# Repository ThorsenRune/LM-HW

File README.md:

# LM-HW
Design files for the LM project
First Version of the LM Hardware

This hardware is part of a neuroprosthesis aimed at restoring hand function in people with tetraplegia.
It is a two channel emg amplifier and a two channel functional electrical stimulator controlled by the ADUCM360 microcontroller.
These are realized using the Eagle version 7 and produced and assembled by EuroCircuits.
The circuits are tested and functional with some minor bug fixes. 

Bug fixes are available upon request

This part of the LM project has been supported by  The Italian Ministry of Health - Ricerca Corrente, the Promobilia Foundation (Sweden) grant no 16066

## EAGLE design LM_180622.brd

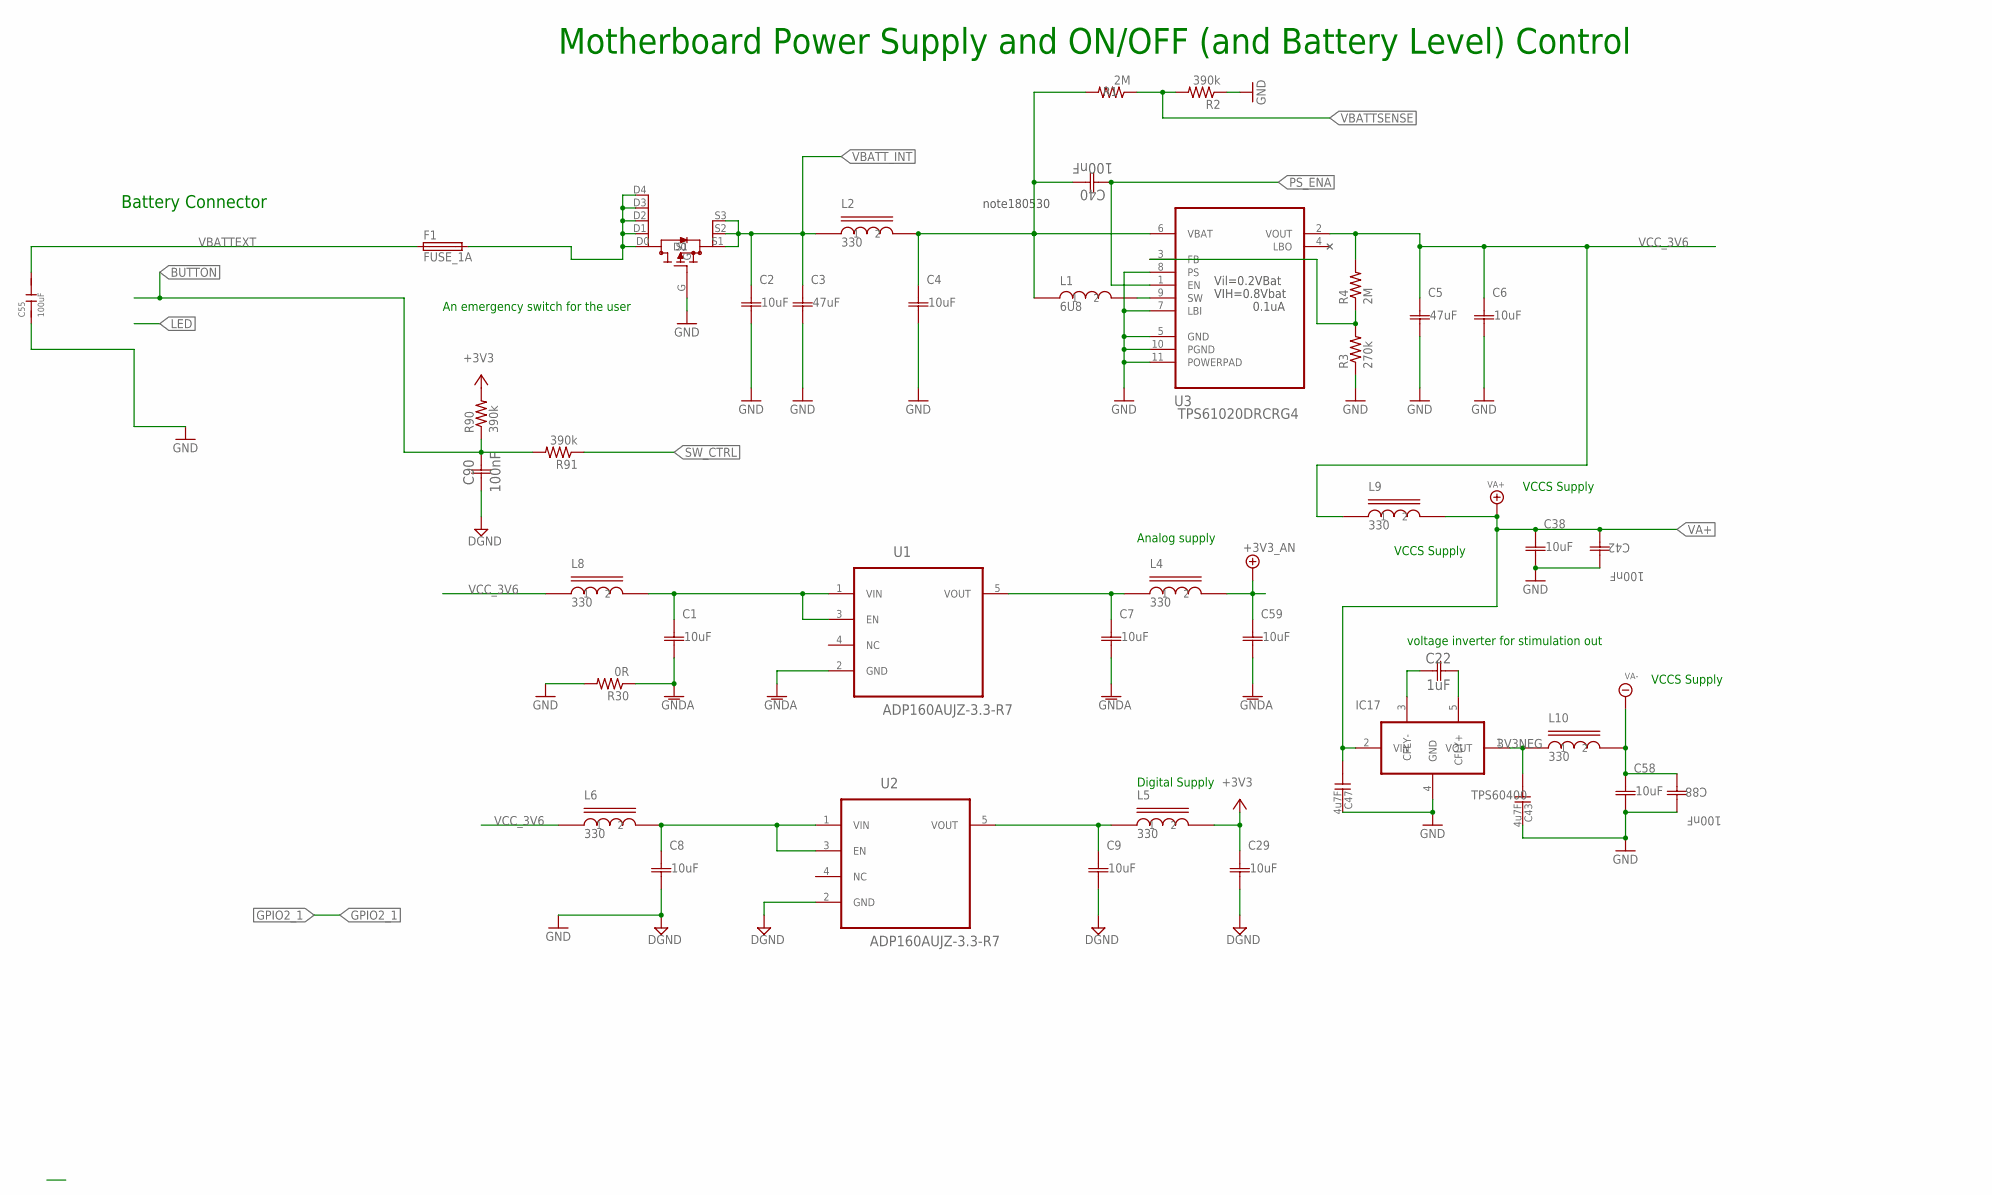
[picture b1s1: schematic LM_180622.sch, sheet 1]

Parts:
C1, C2, C4, C6, C7, C8, C9, C29, C38, C58, C59: 10uF; C0603
C3, C5: 47uF; C0805
C22: 1uF; 0603-CAP
C40, C42, C88, C90: 100nF; C0603
C43, C47: 4u7F; C0805
C55: 100uF; C1210; MPN JMK325BJ107MY-T
F1: FUSE_1A; C0805
IC17: TPS60400; SOT23-5; MPN TPS60400DBVR
L1: 6U8; SMT_POWER_IND_B82462G4; MPN B82462G4682M000
L2, L4, L5, L6, L8, L9, L10: 330; L0603; PARTNO MMZ1608B301C
PMOS1: SIS407DN; POWERPAK1212-8SINGLE
R1, R4: 2M; R0603
R2, R90, R91: 390k; R0603
R3: 270k; R0603; MPN MC0603N270K500CT
R30: 0R; R0603
U1, U2: ADP160AUJZ-3.3-R7; SOT95P280X100-5N; MPN MIC5255-3.3YM5-TR
U3: TPS61020DRCRG4; SON50P300X300X100-11N

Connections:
3V3NEG: C43.1, IC17.1 (VOUT), L10.1
+3V3: C29.2 (C2), L5.2, R90.2; also elsewhere on the board
+3V3_AN: C59.2 (C2), L4.2; also elsewhere on the board
A3V6: C1.2 (C2), L8.2, U1.1 (VIN), U1.3 (EN)
BUTTON: C90.2 (C2), R90.1, R91.2; also elsewhere on the board
FB_3V6: R3.2, R4.1, U3.3 (FB)
GND: C2.1 (C1), C3.1 (C1), C4.1 (C1), C5.1 (C1), C6.1 (C1), C8.1 (C1), C9.1 (C1), C29.1 (C1), C38.1 (C1), C42.2 (C2), C43.2, C47.2, C55.1, C58.1 (C1), C88.2 (C2), C90.1 (C1), IC17.4 (GND), PMOS1.G, R2.1, R3.1, R30.2, U2.2 (GND), U3.5 (GND), U3.7 (LBI), U3.8 (PS), U3.10 (PGND), U3.11 (POWERPAD); also elsewhere on the board
GNDA: C1.1 (C1), C7.1 (C1), C59.1 (C1), R30.1, U1.2 (GND); also elsewhere on the board
unnamed: F1.2, PMOS1.D0, PMOS1.D1, PMOS1.D2, PMOS1.D3, PMOS1.D4
unnamed: L1.2, U3.9 (SW)
unnamed: C7.2 (C2), L4.1, U1.5 (VOUT)
unnamed: C9.2 (C2), L5.1, U2.5 (VOUT)
unnamed: C8.2 (C2), L6.2, U2.1 (VIN), U2.3 (EN)
unnamed: C22.1 (C1), IC17.3 (CFLY-)
unnamed: C22.2 (C2), IC17.5 (CFLY+)
PS_ENA: C40.1 (C1), U3.1 (EN); also elsewhere on the board
SW_CTRL: R91.1; also elsewhere on the board
VA+: C38.2 (C2), C42.1 (C1), C47.1, IC17.2 (VIN), L9.2; also elsewhere on the board
VA-: C58.2 (C2), C88.1 (C1), L10.2; also elsewhere on the board
VBATTEXT: C55.2, F1.1; also elsewhere on the board
VBATTSENSE: R1.1, R2.2; also elsewhere on the board
VBATT_INT: C2.2 (C2), C3.2 (C2), L2.1, PMOS1.S1, PMOS1.S2, PMOS1.S3; also elsewhere on the board
VBATU3: C4.2 (C2), C40.2 (C2), L1.1, L2.2, R1.2, U3.6 (VBAT)
VCC_3V6: C5.2 (C2), C6.2 (C2), L6.1, L8.1, L9.1, R4.2, U3.2 (VOUT)

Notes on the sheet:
Motherboard Power Supply and ON/OFF (and Battery Level) Control
Battery Connector
An emergency switch for the user
voltage inverter for stimulation out
note180530
Vil=0.2VBat
VIH=0.8Vbat
0.1uA
Digital Supply
Analog supply
VCCS Supply

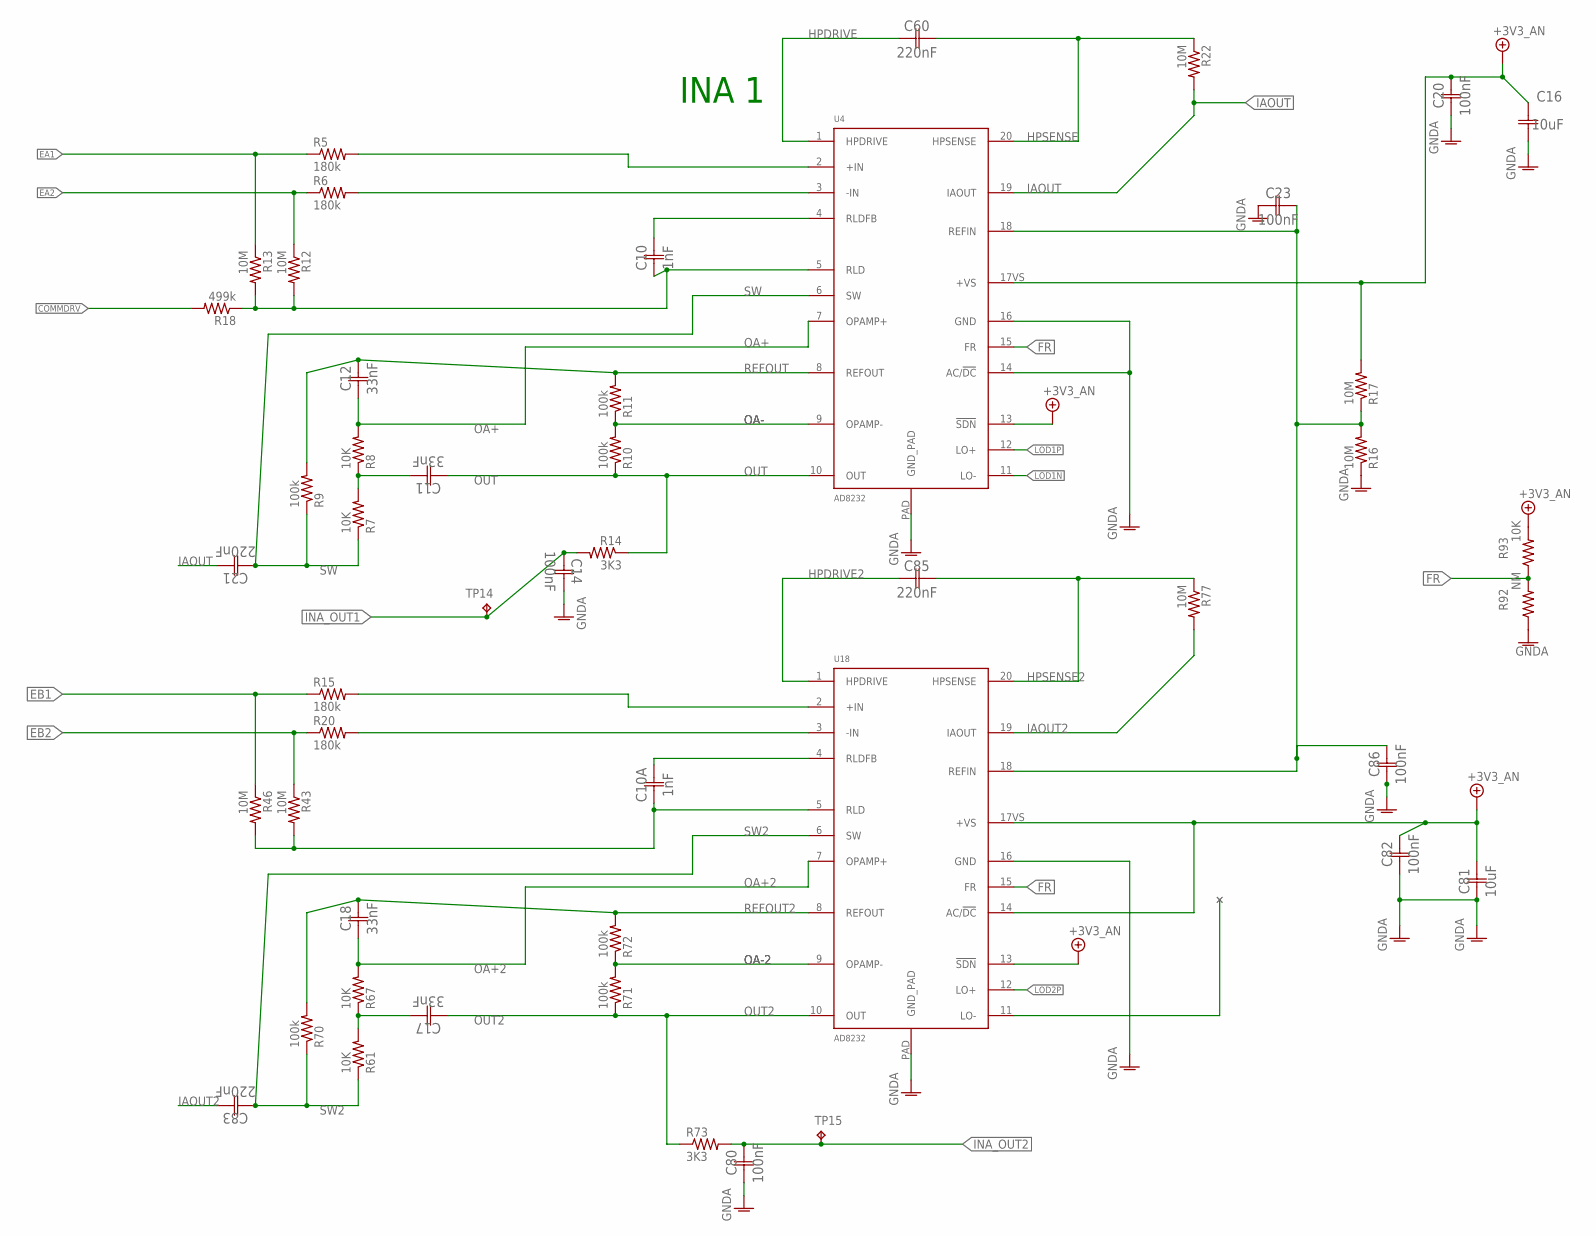
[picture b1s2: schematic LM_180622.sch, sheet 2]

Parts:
C10, C10A: 1nF; C0603
C11, C12, C17, C18: 33nF; C0603
C14, C20, C23, C80, C82, C86: 100nF; C0603
C16, C81: 10uF; C0603
C21, C60, C83, C85: 220nF; C0603
R5, R6, R15, R20: 180k; R0603
R7, R8, R61, R67, R93: 10K; R0603
R9, R10, R11, R70, R71, R72: 100k; R0603
R12, R13, R16, R17, R22, R43, R46, R77: 10M; R0603
R14, R73: 3K3; R0603
R18: 499k; R0603; MPN CRCW0201499KFKED
R92: NM; R0603
TP14, TP15: NM; B1,27
U4, U18: AD8232; LFCSP_20

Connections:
+3V3_AN: C16.2 (C2), C20.1 (C1), C81.2 (C2), C82.1 (C1), R17.2, R93.2, U4.13 (!SDN), U4.17VS (+VS), U18.13 (!SDN), U18.14 (AC/!DC), U18.17VS (+VS); also elsewhere on the board
COMMDRV: R18.2; also elsewhere on the board
EA1: R5.1, R13.1; also elsewhere on the board
EA2: R6.1, R12.1; also elsewhere on the board
EB1: R15.1, R46.1; also elsewhere on the board
EB2: R20.1, R43.1; also elsewhere on the board
FR: R92.2, R93.1, U4.15 (FR), U18.15 (FR)
GNDA: C14.2 (C2), C16.1 (C1), C20.2 (C2), C23.2 (C2), C80.2 (C2), C81.1 (C1), C82.2 (C2), C86.2 (C2), R16.1, R92.1, U4.14 (AC/!DC), U4.16 (GND), U4.PAD (GND_PAD), U18.16 (GND), U18.PAD (GND_PAD); also elsewhere on the board
HPDRIVE: C60.1 (C1), U4.1 (HPDRIVE)
HPDRIVE2: C85.1 (C1), U18.1 (HPDRIVE)
HPSENSE: C60.2 (C2), R22.1, U4.20 (HPSENSE)
HPSENSE2: C85.2 (C2), R77.1, U18.20 (HPSENSE)
IAOUT: C21.1 (C1), R22.2, U4.19 (IAOUT)
IAOUT2: C83.1 (C1), R77.2, U18.19 (IAOUT)
INA_OUT1: C14.1 (C1), R14.2, TP14.TP; also elsewhere on the board
INA_OUT2: C80.1 (C1), R73.2, TP15.TP; also elsewhere on the board
LOD1N: U4.11 (LO-); also elsewhere on the board
LOD1P: U4.12 (LO+); also elsewhere on the board
LOD2P: U18.12 (LO+); also elsewhere on the board
unnamed: R5.2, U4.2 (+IN)
unnamed: R6.2, U4.3 (-IN)
unnamed: C11.1 (C1), R7.2, R8.1
unnamed: C10A.2 (C2), U18.4 (RLDFB)
unnamed: C10A.1 (C1), R43.2, R46.2, U18.5 (RLD)
unnamed: C10.2 (C2), U4.4 (RLDFB)
unnamed: C10.1 (C1), R12.2, R13.2, R18.1, U4.5 (RLD)
unnamed: R15.2, U18.2 (+IN)
unnamed: R20.2, U18.3 (-IN)
unnamed: C17.1 (C1), R61.2, R67.1
OA+: C12.2 (C2), R8.2, U4.7 (OPAMP+)
OA+2: C18.2 (C2), R67.2, U18.7 (OPAMP+)
OA-: R10.2, R11.1, U4.9 (OPAMP-)
OA-2: R71.2, R72.1, U18.9 (OPAMP-)
OUT: C11.2 (C2), R10.1, R14.1, U4.10 (OUT)
OUT2: C17.2 (C2), R71.1, R73.1, U18.10 (OUT)
REFOUT: C12.1 (C1), R9.2, R11.2, U4.8 (REFOUT)
REFOUT2: C18.1 (C1), R70.2, R72.2, U18.8 (REFOUT)
SW: C21.2 (C2), R7.1, R9.1, U4.6 (SW)
SW2: C83.2 (C2), R61.1, R70.1, U18.6 (SW)
VREFIN: C23.1 (C1), C86.1 (C1), R16.2, R17.1, U4.18 (REFIN), U18.18 (REFIN)

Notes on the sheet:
INA 1

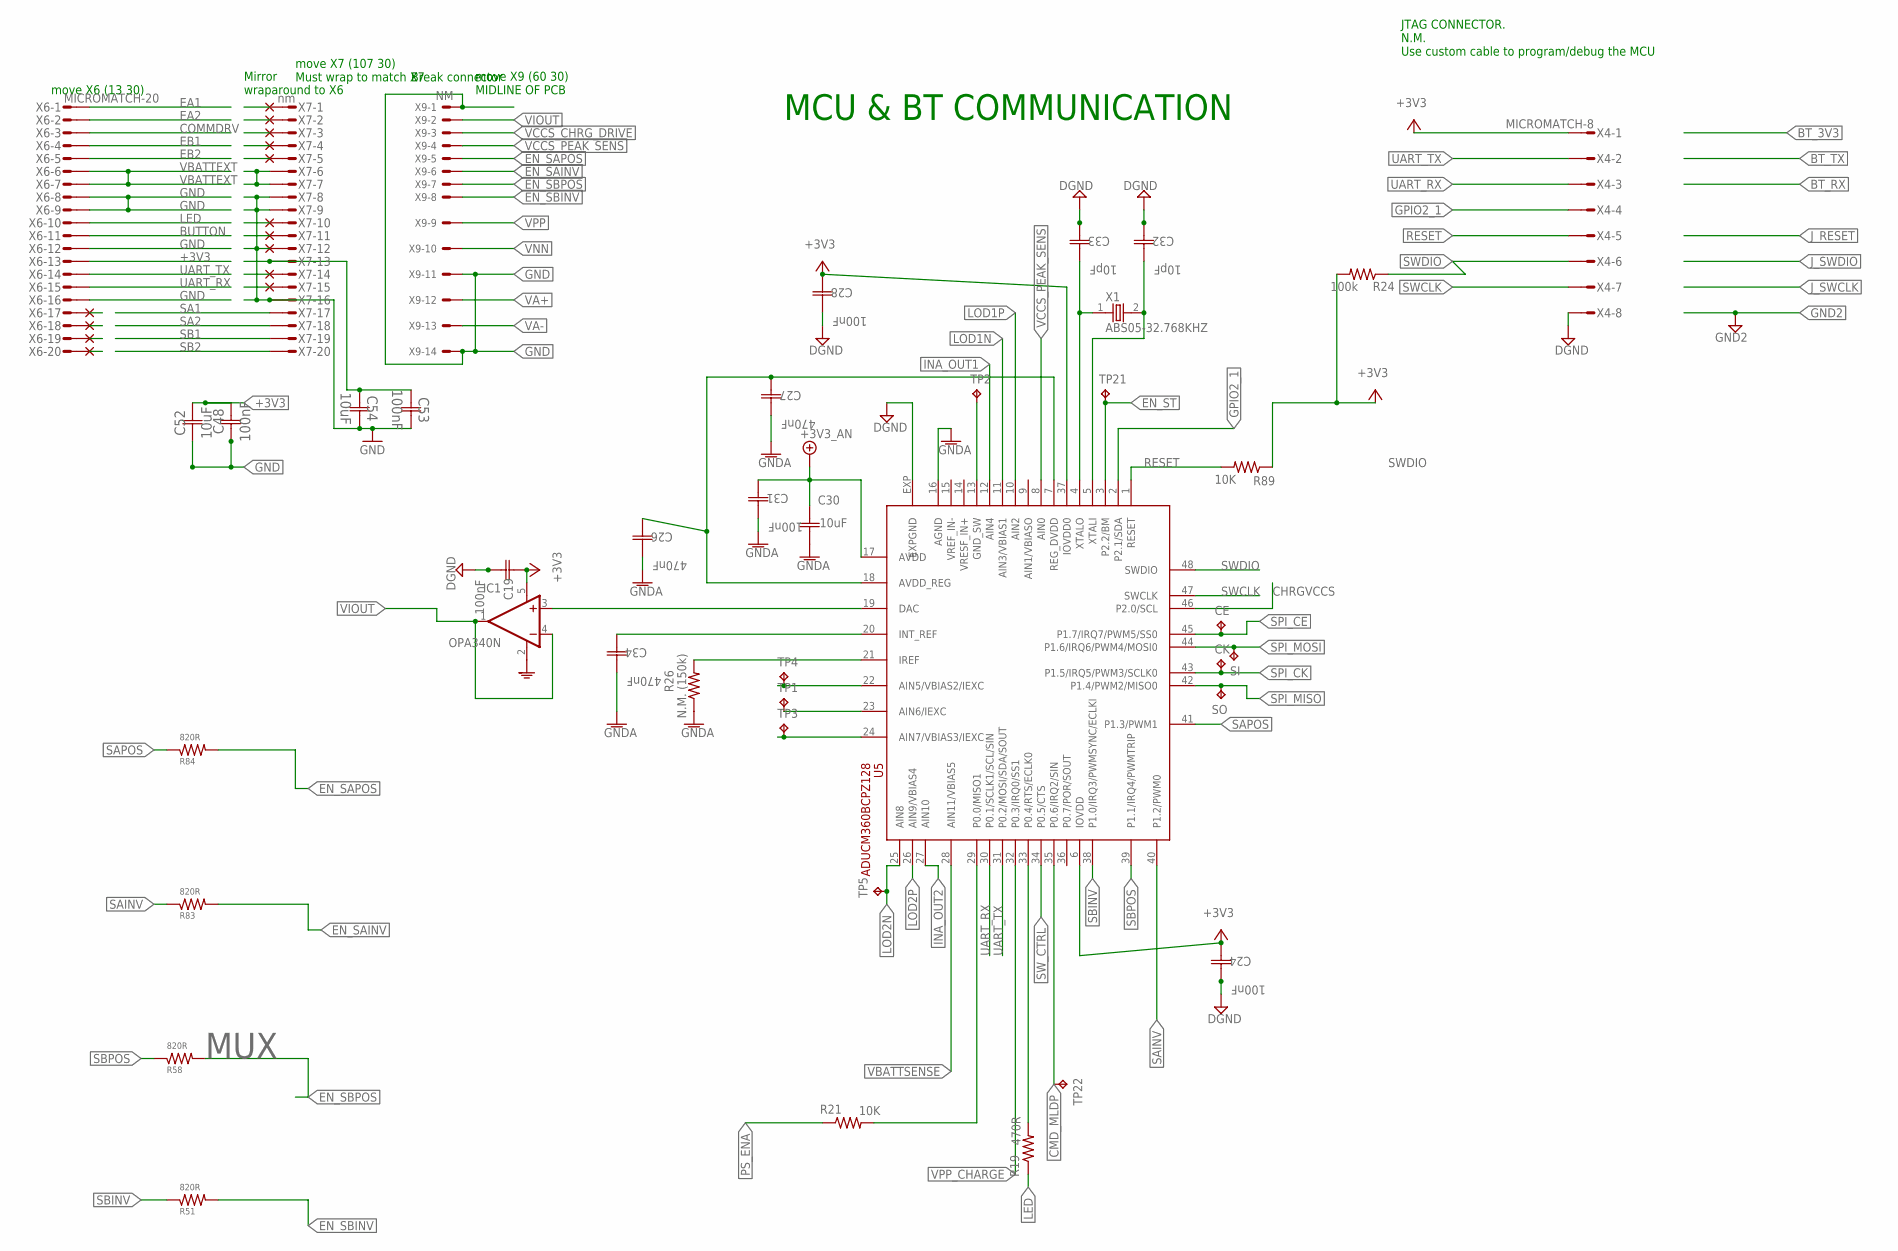
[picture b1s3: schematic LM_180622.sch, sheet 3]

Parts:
C19, C24, C28, C31, C48, C53: 100nF; C0603
C26, C27, C34: 470nF; C0603
C30, C52, C54: 10uF; C0603
C32, C33: 10pF; C0603
CE: NM; TH0305
CK: NM; TH0305
IC1: OPA340N; SOT23-5; MPN OPA340NA/3K
R19: 470R; R0603; MPN ERJ3EKF4700V
R21, R89: 10K; R0603
R24: 100k; R0603
R26: N.M. (150k); R0603
R51, R58, R83, R84: 820R; R0603
SI: NM; TH0305
SO: NM; TH0305
TP1, TP2, TP3, TP4, TP5, TP21, TP22: NM; TH0305
U5: ADUCM360BCPZ128; LFCSP48; MPN ADUCM360BCPZ128
X1: ABS05-32.768KHZ; CRYSTAL-2PIN
X4: MICROMATCH-8
X6: MICROMATCH-20; MPN 2-215079-0
X7: nm; MICROMATCH-20
X9: NM; 70543-14

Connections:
3V3_BT: C53.2 (C2), C54.1 (C1), X7.13
+3V3: C19.1 (C1), C24.1 (C1), C28.1 (C1), C48.1 (C1), C52.2 (C2), IC1.5 (V+), R24.2, R89.1, U5.6 (IOVDD), U5.37 (IOVDD0), X4.1, X6.13; also elsewhere on the board
+3V3_AN: C30.2 (C2), C31.1 (C1), U5.17 (AVDD); also elsewhere on the board
BUTTON: X6.11; also elsewhere on the board
CHRGVCCS: U5.46 (P2.0/SCL); also elsewhere on the board
CMD_MLDP: TP22.TP, U5.35 (P0.6/IRQ2/SIN)
COMMDRV: X6.3; also elsewhere on the board
EA1: X6.1; also elsewhere on the board
EA2: X6.2; also elsewhere on the board
EB1: X6.4; also elsewhere on the board
EB2: X6.5; also elsewhere on the board
EN_SAINV: R83.2, X9.6; also elsewhere on the board
EN_SAPOS: R84.2, X9.5; also elsewhere on the board
EN_SBINV: R51.2, X9.8; also elsewhere on the board
EN_SBPOS: R58.2, X9.7; also elsewhere on the board
EN_ST: TP21.TP, U5.3 (P2.2/BM)
GND: C19.2 (C2), C24.2 (C2), C28.2 (C2), C32.1 (C1), C33.1 (C1), C48.2 (C2), C52.1 (C1), C53.1 (C1), C54.2 (C2), IC1.2 (V-), U5.EXP (EXPGND), X4.8, X6.8, X6.9, X6.12, X6.16, X7.8, X7.9, X7.12, X7.16, X9.1, X9.11, X9.14; also elsewhere on the board
GNDA: C26.2 (C2), C27.2 (C2), C30.1 (C1), C31.2 (C2), C34.2 (C2), R26.1, U5.16 (AGND); also elsewhere on the board
GPIO2_1: U5.2 (P2.1/SDA), X4.4
INA_OUT1: U5.12 (AIN4); also elsewhere on the board
INA_OUT2: U5.27 (AIN10); also elsewhere on the board
LED: R19.1, X6.10
LED_CTRL1: R19.2, U5.33 (P0.4/RTS/ECLK0)
LOD1N: U5.11 (AIN3/VBIAS1); also elsewhere on the board
LOD1P: U5.10 (AIN2); also elsewhere on the board
LOD2N: TP5.TP, U5.25 (AIN8)
LOD2P: U5.26 (AIN9/VBIAS4); also elsewhere on the board
unnamed: C33.2 (C2), U5.4 (XTALO), X1.1
unnamed: C26.1 (C1), C27.1 (C1), U5.7 (REG_DVDD), U5.18 (AVDD_REG)
unnamed: TP1.TP, U5.23 (AIN6/IEXC)
unnamed: C32.2 (C2), U5.5 (XTALI), X1.2
unnamed: R26.2, U5.21 (IREF)
unnamed: C34.1 (C1), U5.20 (INT_REF)
unnamed: R21.2, U5.29 (P0.0/MISO1)
unnamed: TP2.TP, U5.13 (GND_SW)
unnamed: X7.6, X7.7
unnamed: IC1.3 (+IN), U5.19 (DAC)
unnamed: TP3.TP, U5.24 (AIN7/VBIAS3/IEXC)
unnamed: TP4.TP, U5.22 (AIN5/VBIAS2/IEXC)
PS_ENA: R21.1; also elsewhere on the board
RESET: R89.2, U5.1 (RESET), X4.5
SA1: X7.17; also elsewhere on the board
SA2: X7.18; also elsewhere on the board
SAINV: R83.1, U5.40 (P1.2/PWM0)
SAPOS: R84.1, U5.41 (P1.3/PWM1)
SB1: X7.19; also elsewhere on the board
SB2: X7.20; also elsewhere on the board
SBINV: R51.1, U5.38 (P1.0/IRQ3/PWMSYNC/ECLKI)
SBPOS: R58.1, U5.39 (P1.1/IRQ4/PWMTRIP)
SPI_CE: CE.TP, U5.45 (P1.7/IRQ7/PWM5/SS0)
SPI_CK: CK.TP, U5.43 (P1.5/IRQ5/PWM3/SCLK0)
SPI_MISO: SO.TP, U5.42 (P1.4/PWM2/MISO0)
SPI_MOSI: SI.TP, U5.44 (P1.6/IRQ6/PWM4/MOSI0)
SWCLK: U5.47 (SWCLK), X4.7
SWDIO: R24.1, U5.48 (SWDIO), X4.6
SW_CTRL: U5.34 (P0.5/CTS); also elsewhere on the board
UART_RX: U5.30 (P0.1/SCLK1/SCL/SIN), X4.3, X6.15
UART_TX: U5.31 (P0.2/MOSI/SDA/SOUT), X4.2, X6.14
VA+: X9.12; also elsewhere on the board
VA-: X9.13; also elsewhere on the board
VBATTEXT: X6.6, X6.7; also elsewhere on the board
VBATTSENSE: U5.28 (AIN11/VBIAS5); also elsewhere on the board
VCCS_CHRG_DRIVE: X9.3; also elsewhere on the board
VCCS_PEAK_SENS: U5.8 (AIN0), X9.4; also elsewhere on the board
VIOUT: IC1.1 (OUT), IC1.4 (-IN), X9.2; also elsewhere on the board
VNN: X9.10; also elsewhere on the board
VPP: X9.9; also elsewhere on the board
VPP_CHARGE: U5.32 (P0.3/IRQ0/SS1); also elsewhere on the board

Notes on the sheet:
MCU & BT COMMUNICATION
JTAG CONNECTOR. N.M. Use custom cable to program/debug the MCU
MUX
Break connector
Mirror wraparound to X6
move X9 (60 30) MIDLINE OF PCB
move X6 (13 30)
move X7 (107 30) Must wrap to match X7

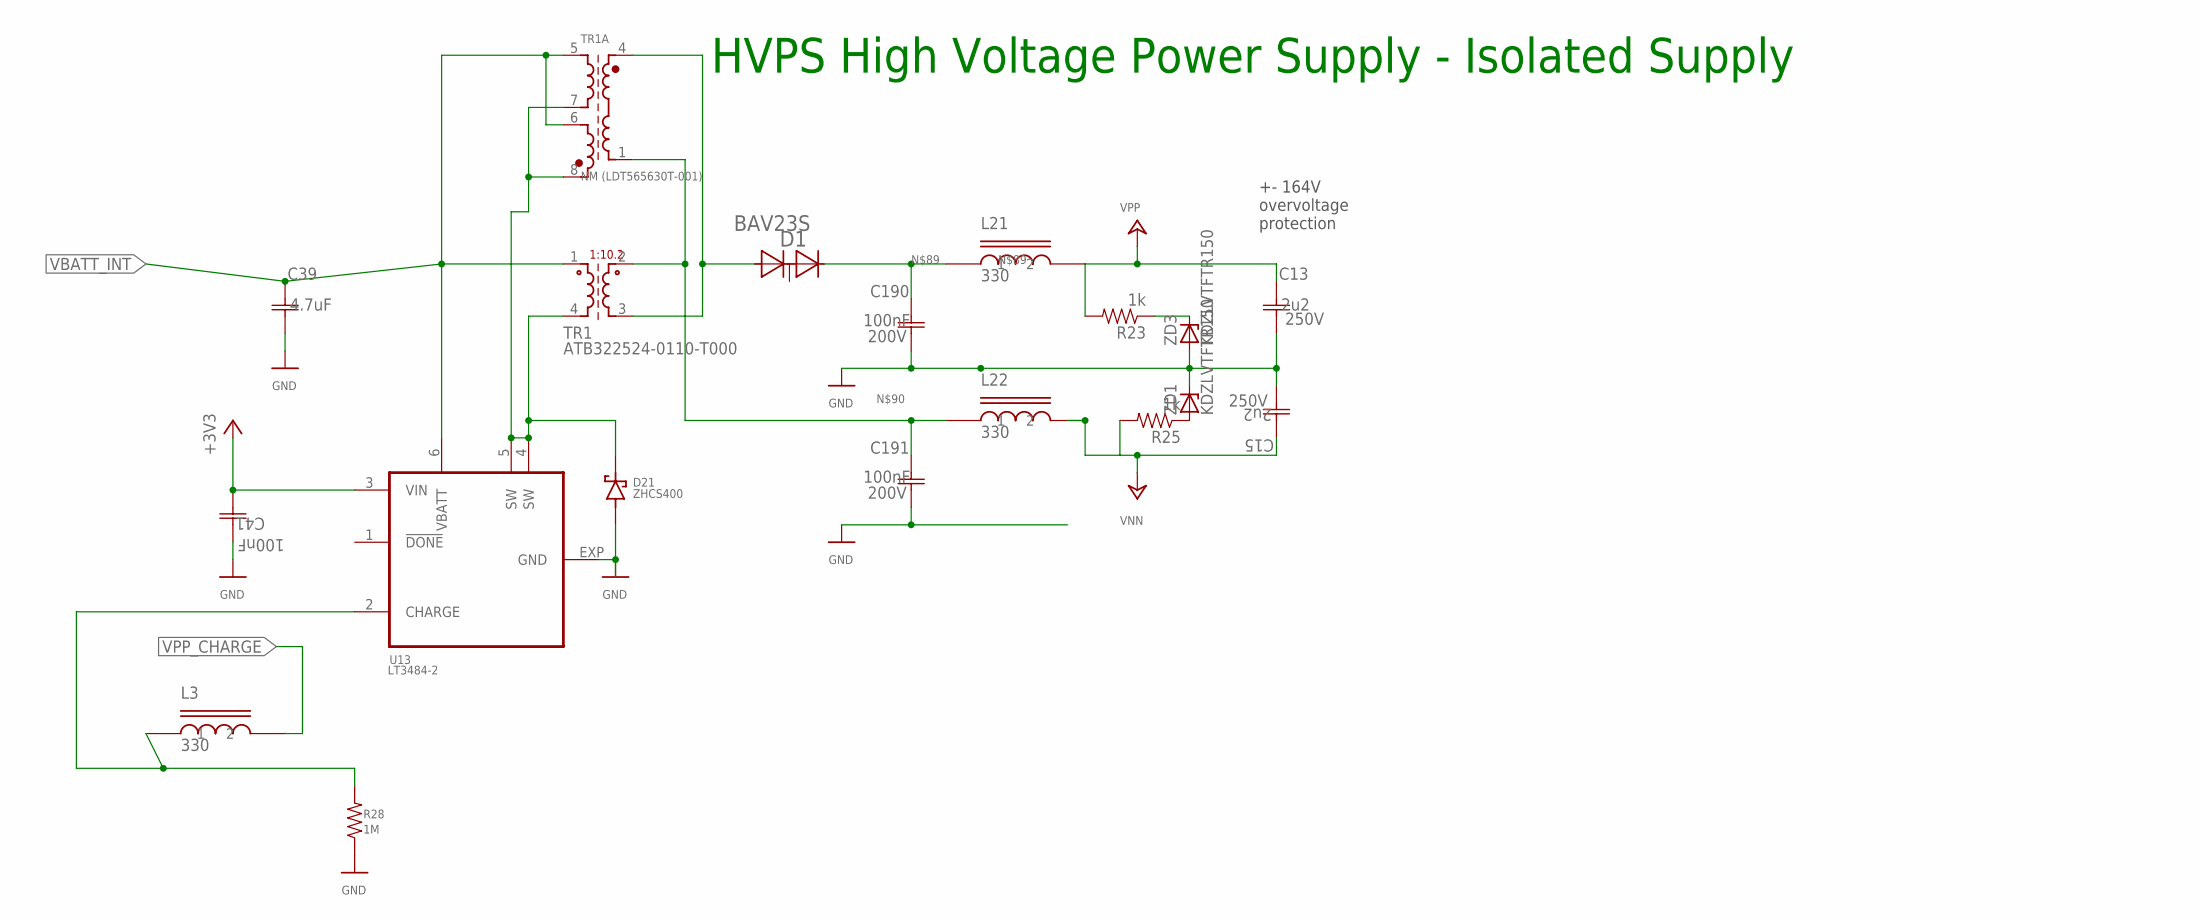
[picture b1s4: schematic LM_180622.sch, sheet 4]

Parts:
C13, C15: 2u2; C2220K; MPN ECA-2GHG2R2
C39: 4.7uF; C0603
C41: 100nF; C0603
C190, C191: 100nF; 1206
D1: BAV23S; SOT23; MPN BAV23S-7-F
D21: ZHCS400; SOD323
L3, L21, L22: 330; L0603; PARTNO MMZ1608B301C
R23, R25: 1k; R0603
R28: 1M; R0603
TR1: ATB322524-0110-T000; 3225_4PIN
TR1A: NM (LDT565630T-001); SM-E6
U13: LT3484-2; DFN6-2X3
ZD1, ZD3: KDZLVTFTR150; SOD123

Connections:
+3V3: C41.1 (C1), U13.3 (VIN); also elsewhere on the board
GND: C13.1 (C1), C15.1 (C1), C39.1 (C1), C41.2 (C2), C190.1 (C1), C191.1 (C1), D21.A (1A), R28.1, U13.EXP (GND), ZD1.1C (C), ZD3.2A (A); also elsewhere on the board
LT_CHRG: L3.1, R28.2, U13.2 (CHARGE)
unnamed: R23.1, ZD3.1C (C)
unnamed: R25.1, ZD1.2A (A)
unnamed: D1.1, TR1.3, TR1A.4
unnamed: C190.2 (C2), D1.2, L21.1
unnamed: C191.2 (C2), L22.1, TR1.2, TR1A.1
N_SW2: D21.K (2C), TR1.4, TR1A.7, TR1A.8, U13.4 (SW), U13.5 (SW)
VBATT_INT: C39.2 (C2), TR1.1, TR1A.5, TR1A.6, U13.6 (VBATT); also elsewhere on the board
VNN: C15.2 (C2), L22.2, R25.2; also elsewhere on the board
VPP: C13.2 (C2), L21.2, R23.2; also elsewhere on the board
VPP_CHARGE: L3.2; also elsewhere on the board

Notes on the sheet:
HVPS High Voltage Power Supply - Isolated Supply
+- 164V overvoltage protection

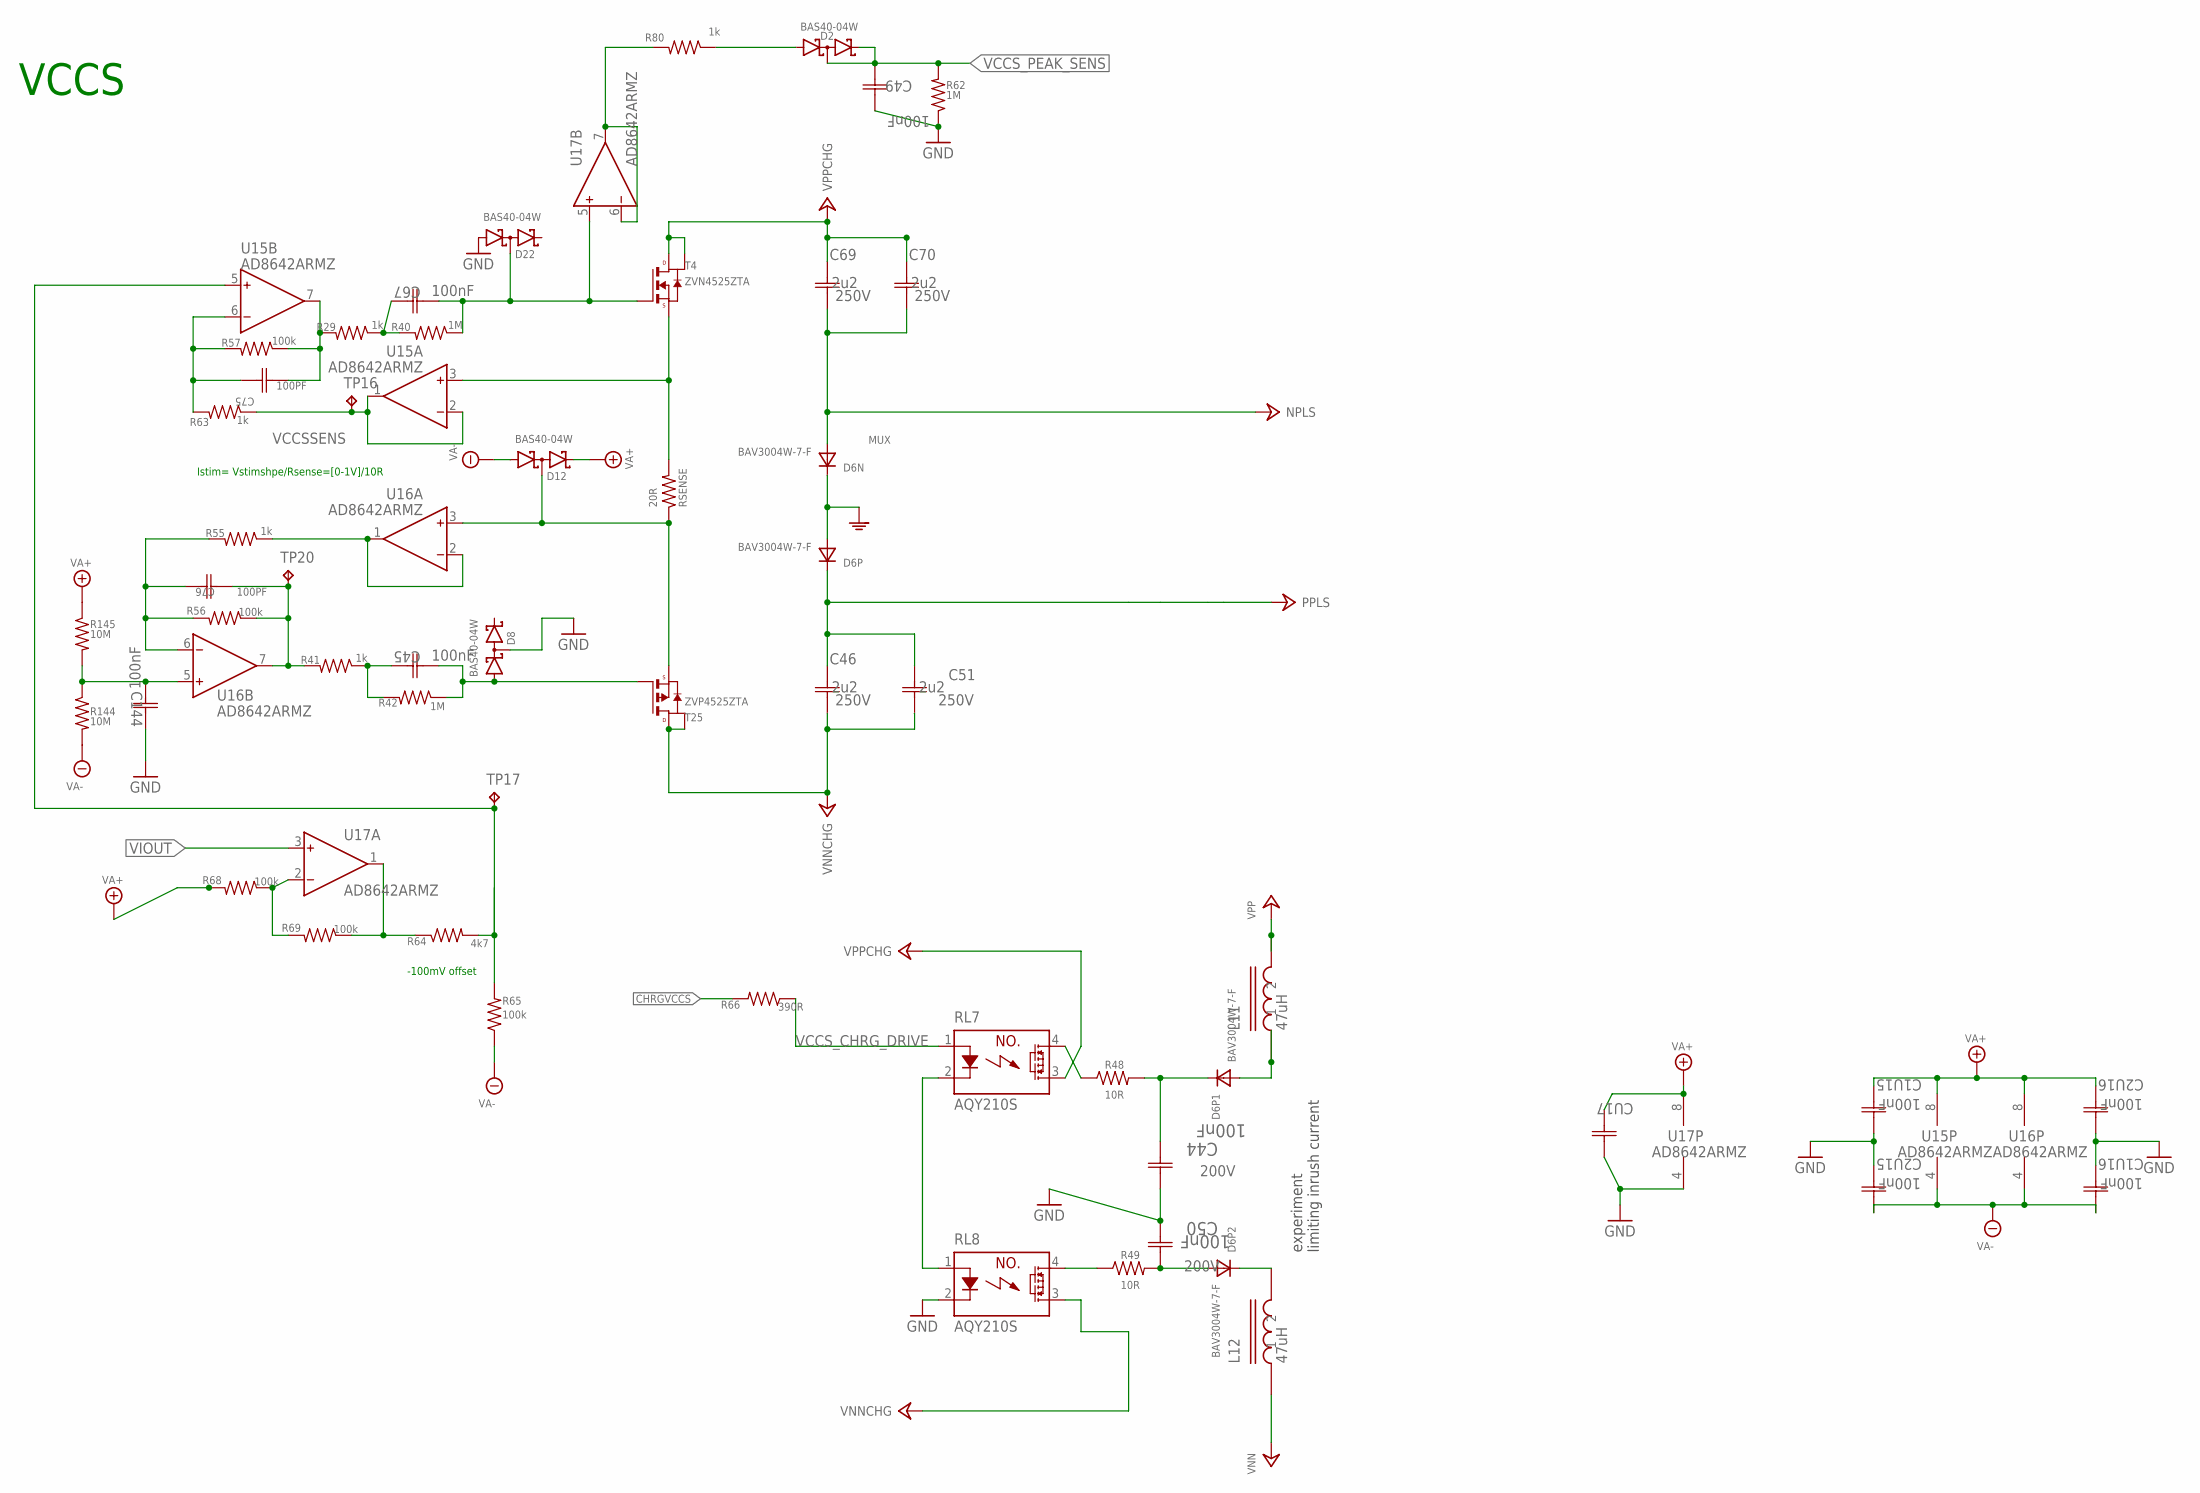
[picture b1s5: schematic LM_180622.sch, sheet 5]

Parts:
C1U15, C1U16, C2U15, C2U16, C45, C49, C67, C144: 100nF; C0603
C44, C50: 100nF; 1206
C46, C51, C69, C70: 2u2; C2220K; MPN ECA-2GHG2R2
C75, C76: 100PF; C0603
CU17: 100nF; C0603
D2, D8, D12, D22: BAS40-04W; SOT323; MPN BAS40-04W 115.
D6N, D6P, D6P1, D6P2: BAV3004W-7-F; SOD123
L11, L12: 47uH; 1206
R29, R41, R55, R63, R80: 1k; R0603
R40, R42, R62: 1M; R0603
R48, R49: 10R; R0603
R56, R57, R65, R68, R69: 100k; R0603
R64: 4k7; R0603
R66: 390R; R0603
R144, R145: 10M; R0603
RL7, RL8: AQY210S; SOP04; MPN AQY210SX
RSENSE: 20R; R2010
T4: ZVN4525ZTA; SOT89
T25: ZVP4525ZTA; SOT89
TP16, TP17, TP20: NM; TH0305
U15, U16, U17: AD8642ARMZ; MSOP8

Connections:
CHRGVCCS: R66.2; also elsewhere on the board
GND: C1U15.1 (C1), C1U16.2 (C2), C2U15.2 (C2), C2U16.1 (C1), C44.1 (C1), C49.2 (C2), C50.2 (C2), C144.1 (C1), CU17.1 (C1), D6N.C, D6P.A, D8.3 (C1A2), D22.1 (A1), R62.1, RL8.2 (K), U17.4 (V-); also elsewhere on the board
unnamed: C75.2 (C2), R29.2, R57.1, U15.7 (OUT)
unnamed: R80.2, U17.6 (IN-), U17.7 (OUT)
unnamed: D6P2.C, L12.2
unnamed: C50.1 (C1), D6P2.A, R49.2
unnamed: D6P1.A, L11.1
unnamed: C44.2 (C2), D6P1.C, R48.2
unnamed: C76.2 (C2), R41.2, R56.1, TP20.TP, U16.7 (OUT)
unnamed: R55.1, U16.1 (OUT), U16.2 (IN-)
unnamed: C76.1 (C1), R55.2, R56.2, U16.6 (IN-)
unnamed: C75.1 (C1), R57.2, R63.2, U15.6 (IN-)
unnamed: R64.1, R69.1, U17.1 (OUT)
unnamed: C144.2 (C2), R144.1, R145.2, U16.5 (IN+)
unnamed: C67.1 (C1), R29.1, R40.2
unnamed: R68.1, R69.2, U17.2 (IN-)
unnamed: R49.1, RL8.4 (DS1)
unnamed: D2.1 (A1), R80.1
unnamed: R48.1, RL7.4 (DS1)
unnamed: C45.1 (C1), R41.1, R42.2
NAQY: RL7.2 (K), RL8.1 (A)
NG1B: C67.2 (C2), D22.3 (C1A2), R40.1, T4.1 (G), U17.5 (IN+)
NG1B1: C45.2 (C2), D8.1 (A1), R42.1, T25.1 (G)
NPLS: C69.1 (C1), C70.1 (C1), D6N.A; also elsewhere on the board
NS1A: D12.3 (C1A2), RSENSE.1, T25.3 (S), U16.3 (IN+)
NSB: RSENSE.2, T4.3 (S), U15.3 (IN+)
PLSCTRL1: R64.2, R65.2, TP17.TP, U15.5 (IN+)
PPLS: C46.2 (C2), C51.2 (C2), D6P.C; also elsewhere on the board
VA+: C1U15.2 (C2), C2U16.2 (C2), CU17.2 (C2), D12.2 (C2), R68.2, R145.1, U15.8 (V+), U16.8 (V+), U17.8 (V+); also elsewhere on the board
VA-: C1U16.1 (C1), C2U15.1 (C1), D12.1 (A1), R65.1, R144.2, U15.4 (V-), U16.4 (V-); also elsewhere on the board
VCCSSENS: R63.1, TP16.TP, U15.1 (OUT), U15.2 (IN-)
VCCS_CHRG_DRIVE: R66.1, RL7.1 (A); also elsewhere on the board
VCCS_PEAK_SENS: C49.1 (C1), D2.2 (C2), D2.3 (C1A2), R62.2; also elsewhere on the board
VIOUT: U17.3 (IN+); also elsewhere on the board
VNN: L12.1; also elsewhere on the board
VNNCHG: C46.1 (C1), C51.1 (C1), RL8.3 (DS2), T25.2 (D2), T25.4 (D3)
VPP: L11.2; also elsewhere on the board
VPPCHG: C69.2 (C2), C70.2 (C2), RL7.3 (DS2), T4.2 (D1), T4.4 (D2)

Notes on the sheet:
VCCS
Istim= Vstimshpe/Rsense=[0-1V]/10R
MUX
-100mV offset
experiment limiting inrush current

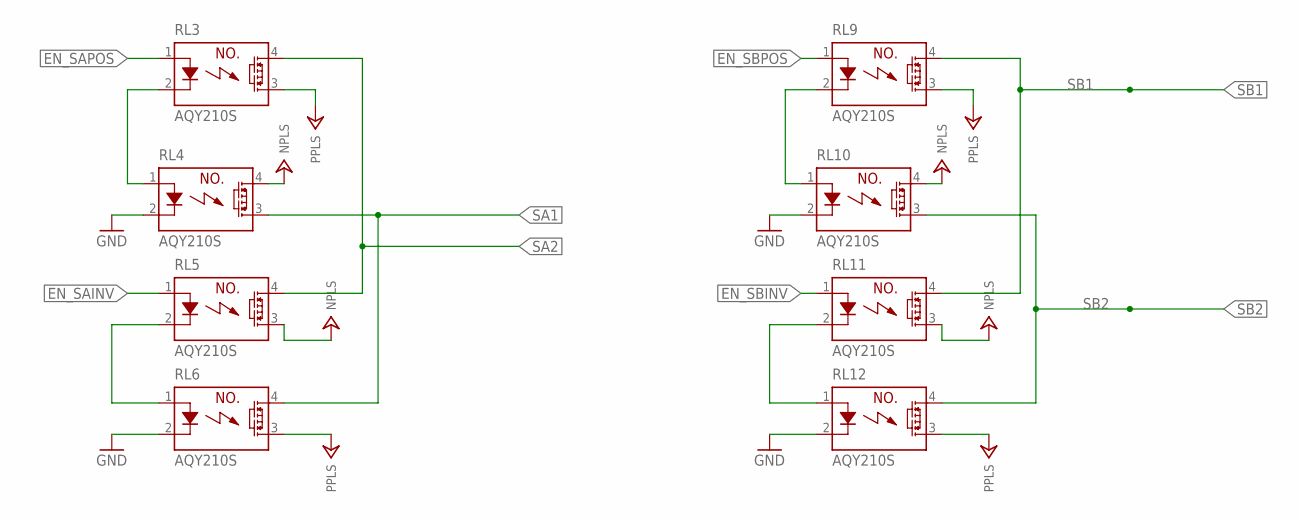
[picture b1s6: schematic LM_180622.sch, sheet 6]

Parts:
RL3, RL4, RL5, RL6, RL9, RL10, RL11, RL12: AQY210S; SOP04; MPN AQY210SX

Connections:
EN_SAINV: RL5.1 (A); also elsewhere on the board
EN_SAPOS: RL3.1 (A); also elsewhere on the board
EN_SBINV: RL11.1 (A); also elsewhere on the board
EN_SBPOS: RL9.1 (A); also elsewhere on the board
GND: RL4.2 (K), RL6.2 (K), RL10.2 (K), RL12.2 (K); also elsewhere on the board
unnamed: RL3.2 (K), RL4.1 (A)
unnamed: RL5.2 (K), RL6.1 (A)
unnamed: RL9.2 (K), RL10.1 (A)
unnamed: RL11.2 (K), RL12.1 (A)
NPLS: RL4.4 (DS1), RL5.3 (DS2), RL10.4 (DS1), RL11.3 (DS2); also elsewhere on the board
PPLS: RL3.3 (DS2), RL6.3 (DS2), RL9.3 (DS2), RL12.3 (DS2); also elsewhere on the board
SA1: RL4.3 (DS2), RL6.4 (DS1); also elsewhere on the board
SA2: RL3.4 (DS1), RL5.4 (DS1); also elsewhere on the board
SB1: RL9.4 (DS1), RL11.4 (DS1); also elsewhere on the board
SB2: RL10.3 (DS2), RL12.4 (DS1); also elsewhere on the board
